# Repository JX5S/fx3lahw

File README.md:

# fx3lahw
Cypress FX3-based USB3 16ch 100Msps logic analyzer

Warning: current revision doesn't work

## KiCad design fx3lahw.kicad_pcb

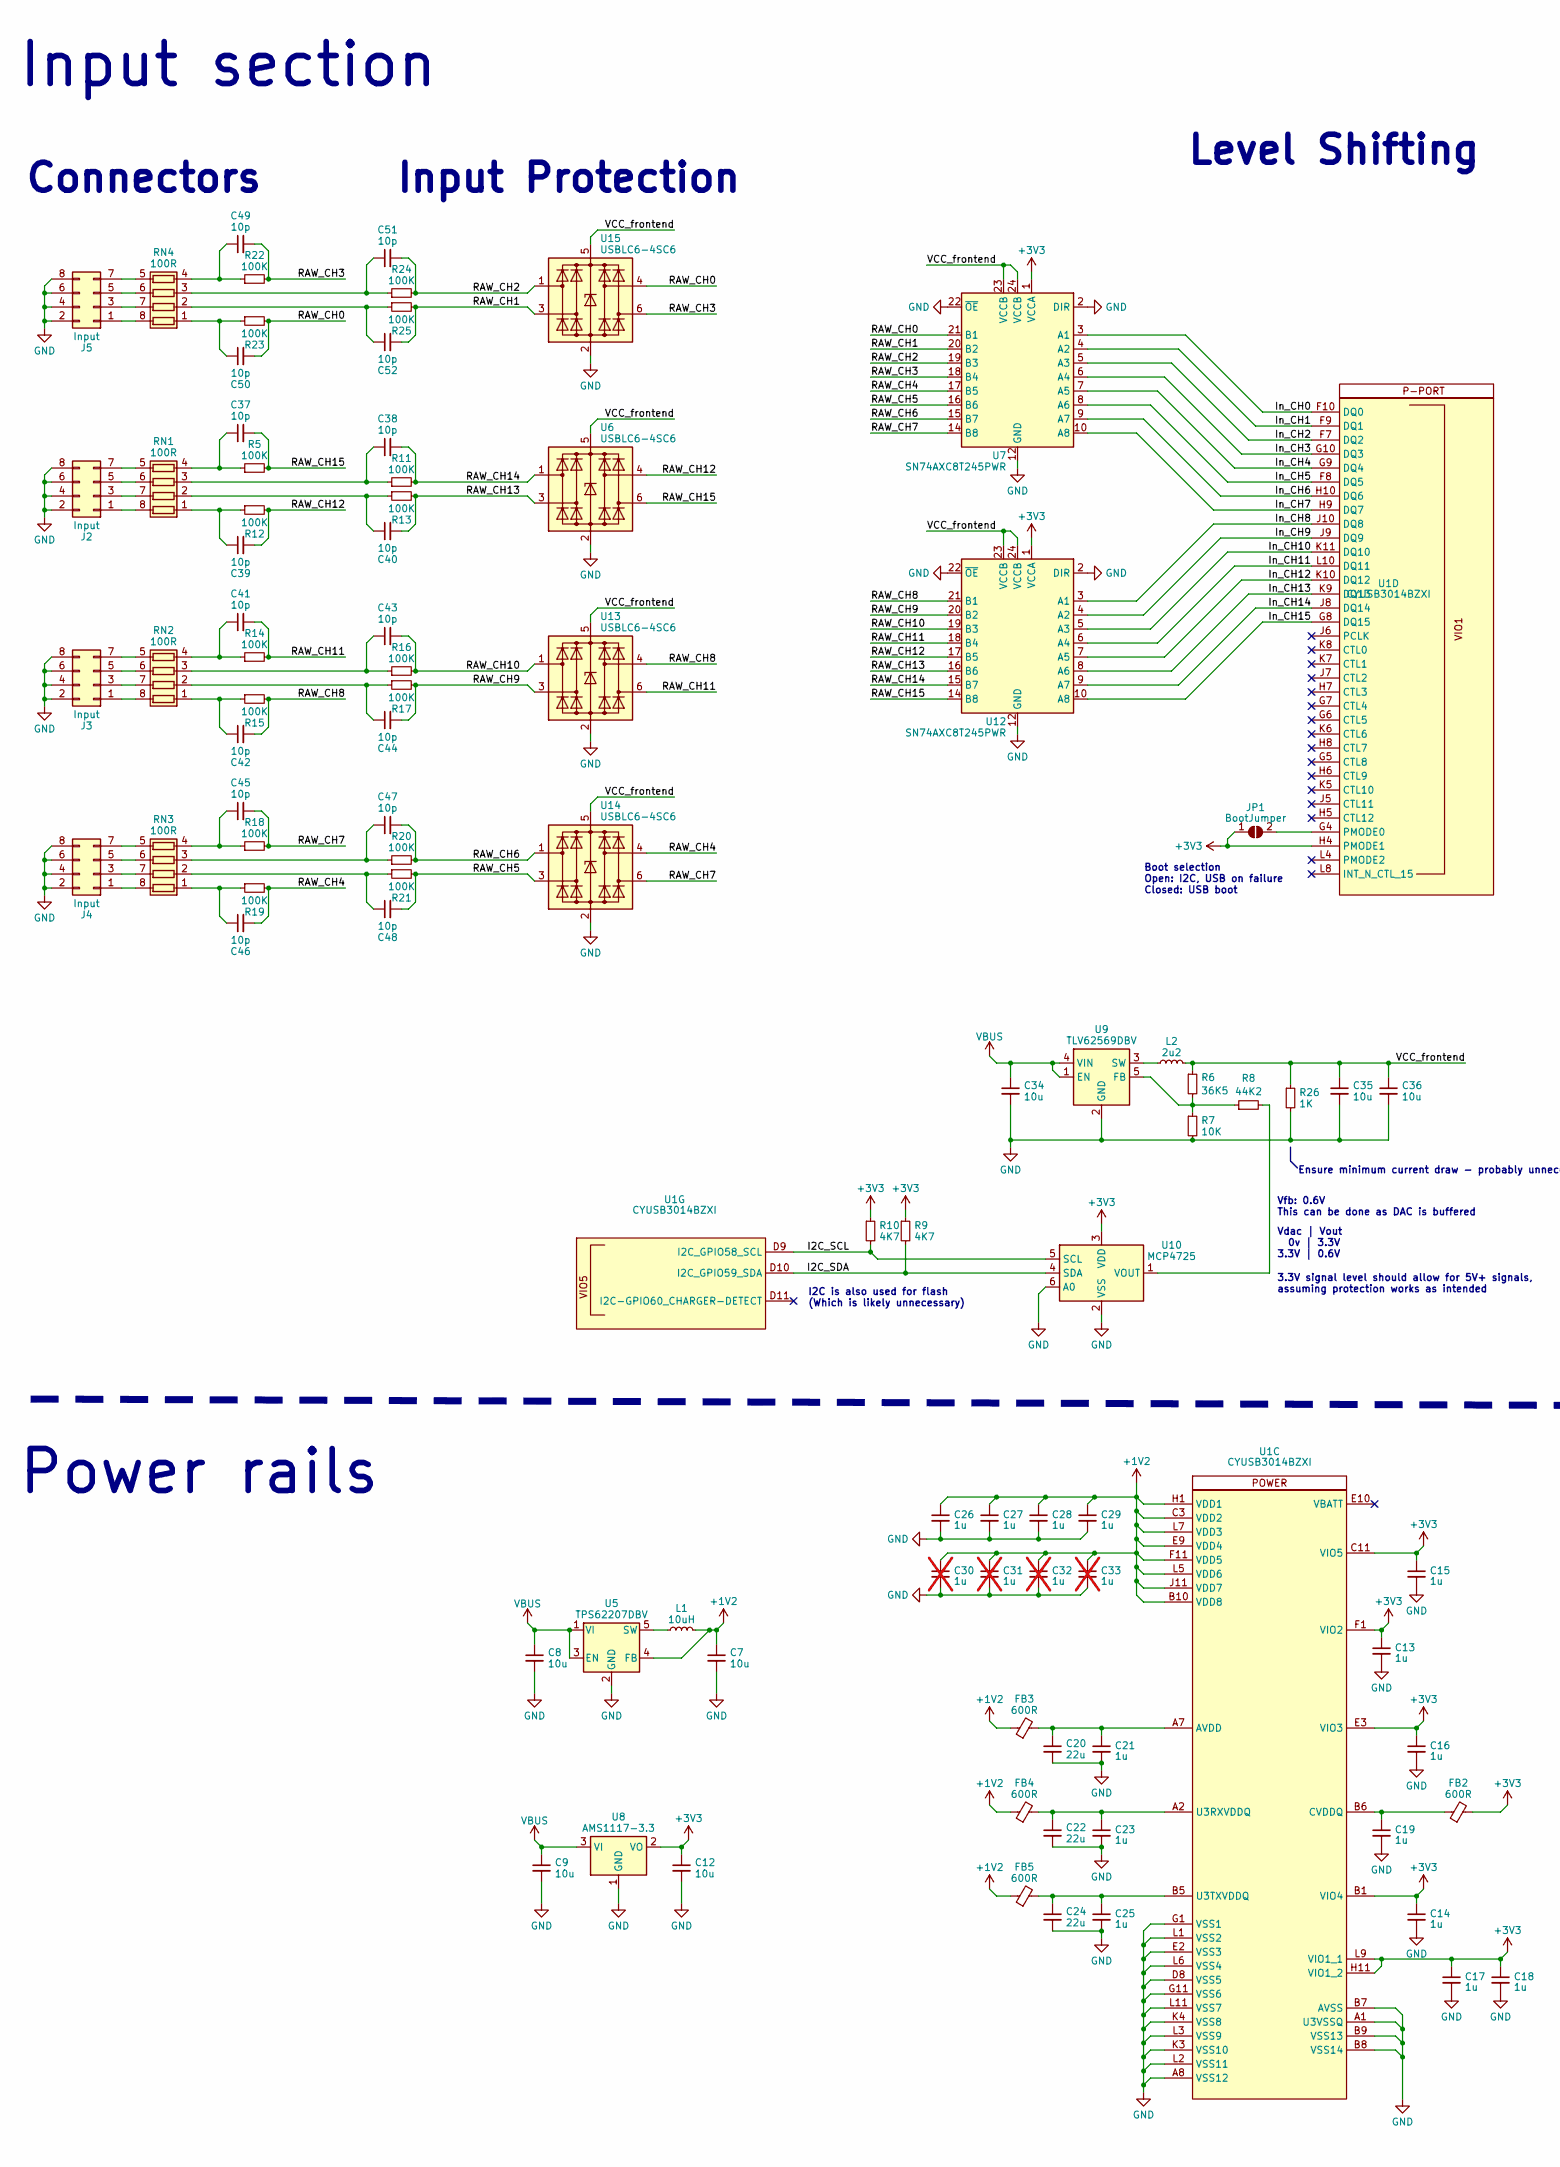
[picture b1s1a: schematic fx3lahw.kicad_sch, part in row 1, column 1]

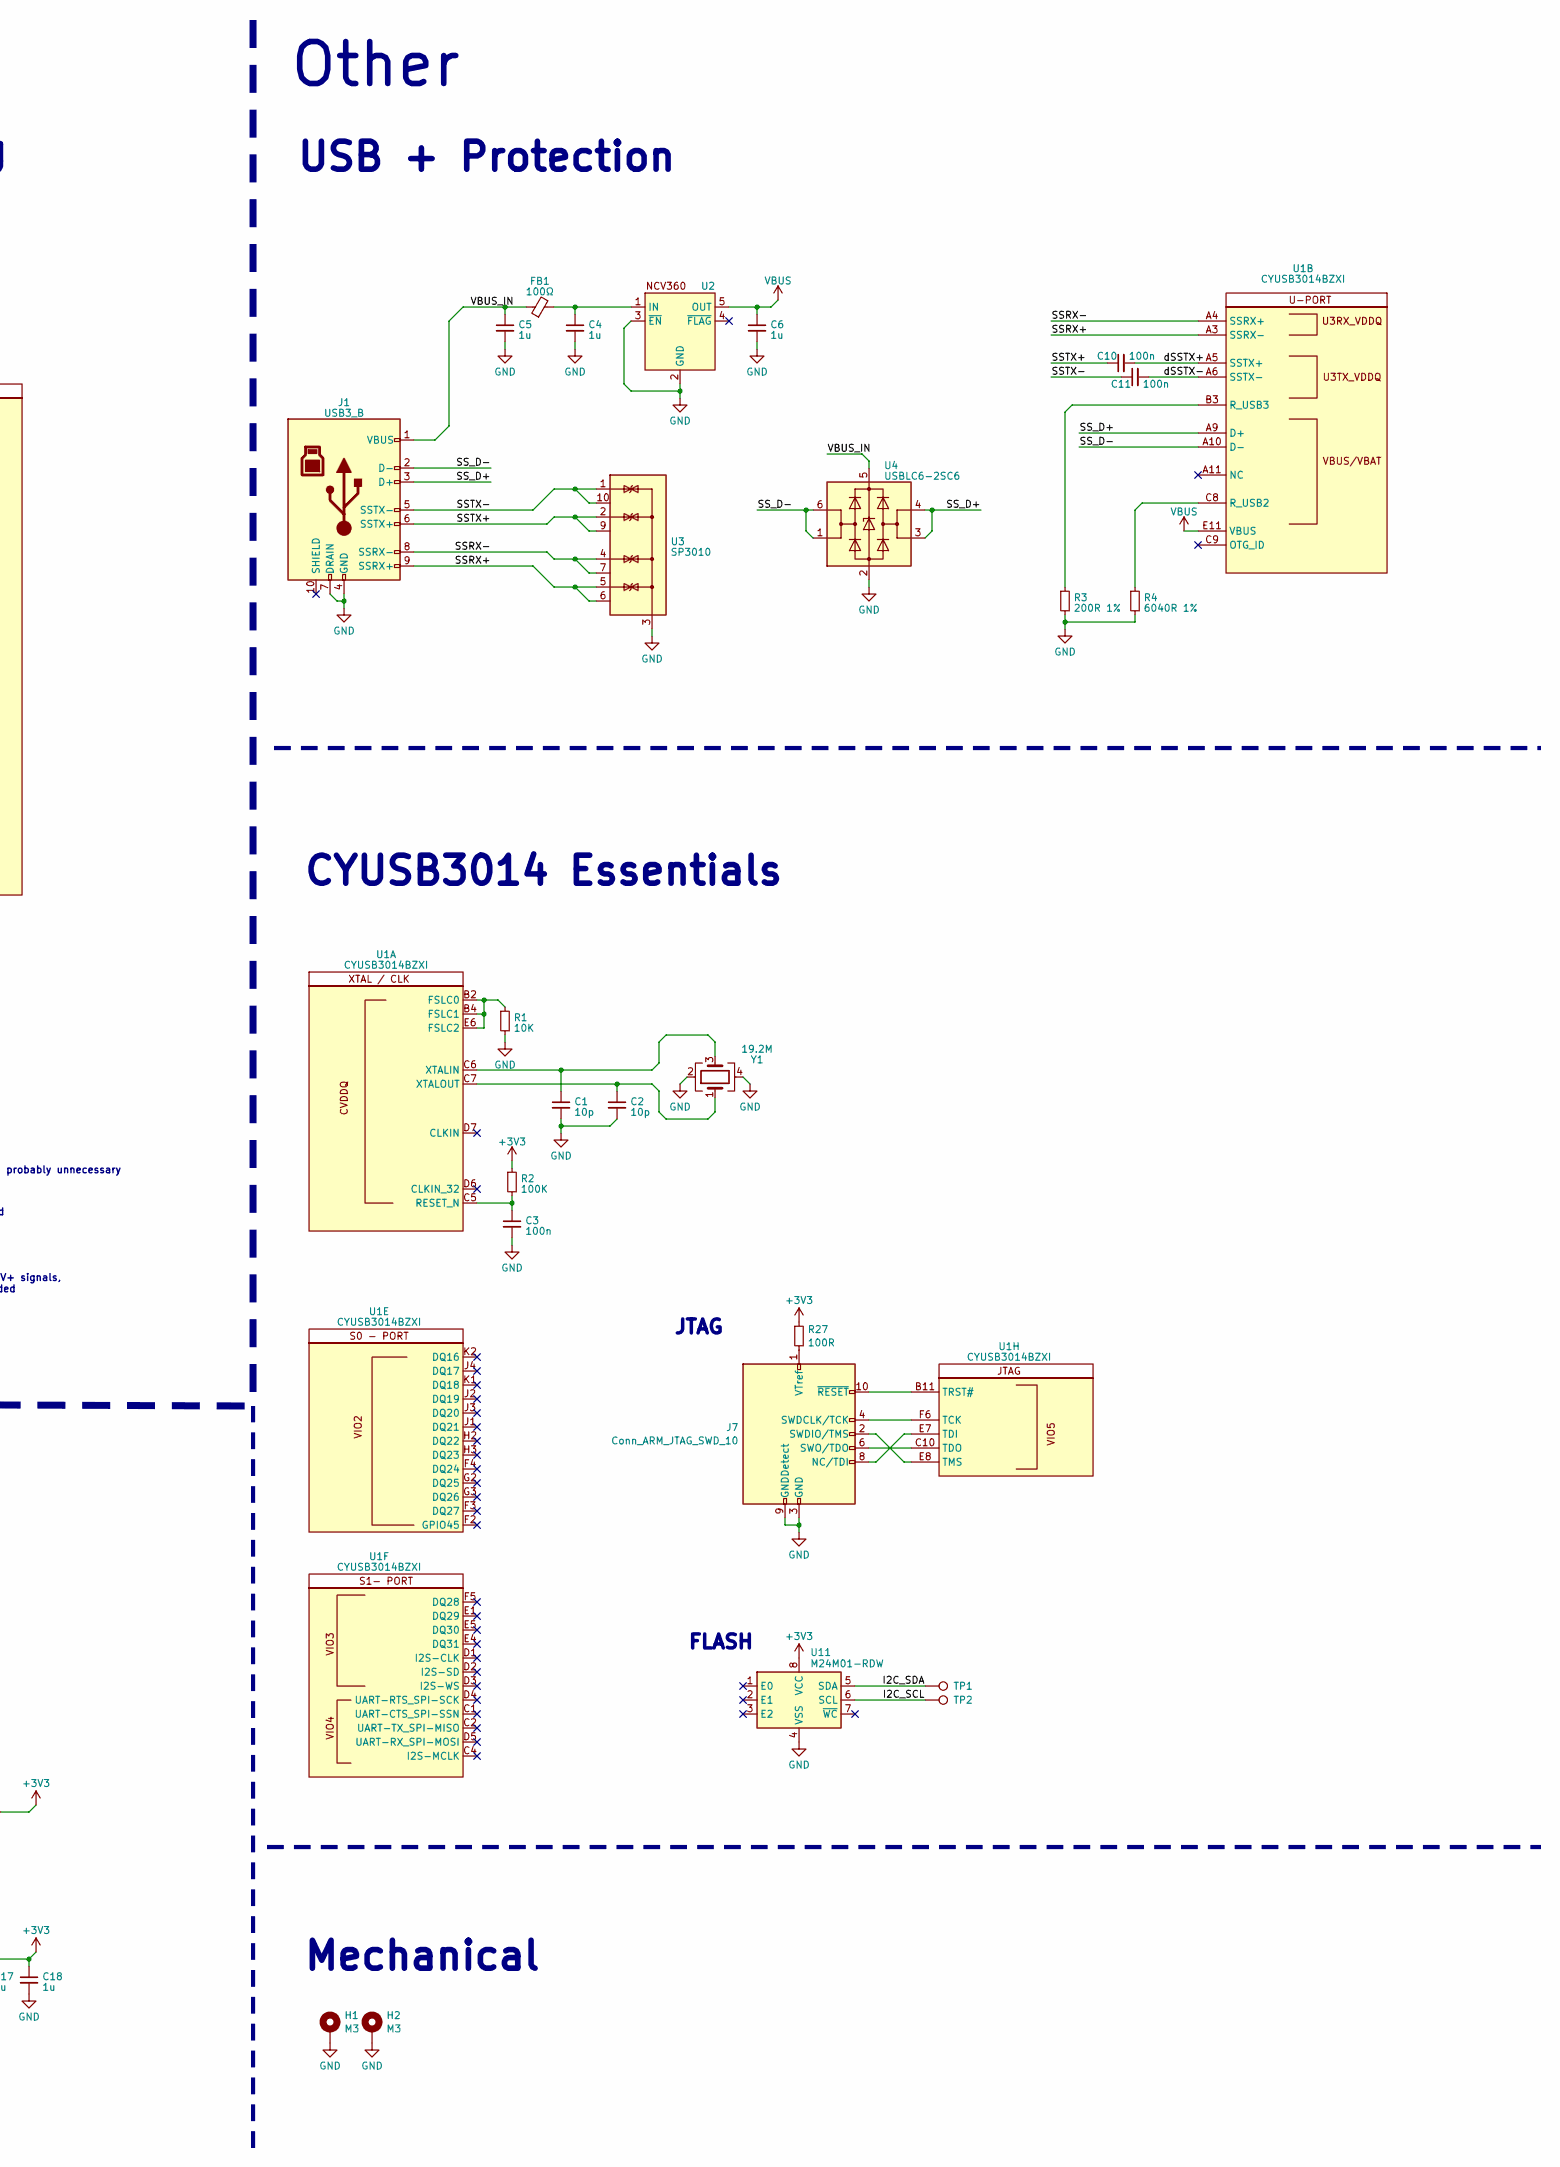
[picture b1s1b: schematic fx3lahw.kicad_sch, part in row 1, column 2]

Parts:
C1, C2, C37, C38, C39, C40, C41, C42, C43, C44, C45, C46, C47, C48, C49, C50, C51, C52: 10p; C_0402_1005Metric; LCSC C1576
C3, C10, C11: 100n; C_0402_1005Metric; LCSC C307331
C4, C5, C6: 1u; C_0603_1608Metric; LCSC C15849
C7, C8, C9, C12: 10u; C_0603_1608Metric; LCSC C19702
C13, C14, C15, C16, C17, C18, C19, C21, C23, C25, C26, C27, C28, C29: 1u; C_0402_1005Metric; LCSC C52923
C20, C22, C24: 22u; C_0603_1608Metric; LCSC C59461
C30, C31, C32, C33: 1u; C_0402_1005Metric; LCSC C52923; not fitted
C34, C35, C36: 10u; C_0603_1608Metric; LCSC C96446
FB1: 100Ω; R_0805_2012Metric; LCSC C1015
FB2, FB3, FB4, FB5: 600R; R_0603_1608Metric; LCSC C1002
H1, H2: M3; MountingHole_3.2mm_M3_Pad; LCSC .
J1: USB3_B; USB3_typeB; LCSC C105423
J2, J3, J4, J5: Input; PinHeader_2x04_P2.54mm_Horizontal; LCSC C492432
J7: Conn_ARM_JTAG_SWD_10; PinHeader_2x05_P1.27mm_Vertical_SMD; LCSC C2935458
JP1: BootJumper; SolderJumper-2_P1.3mm_Open_RoundedPad1.0x1.5mm
L1: 10uH; L_Sunlord_SWPA252012S; LCSC C88532
L2: 2u2; L_Sunlord_SWPA252012S; LCSC C88527
R1, R7: 10K; R_0402_1005Metric; LCSC C25744
R2, R5, R11, R12, R13, R14, R15, R16, R17, R18, R19, R20, R21, R22, R23, R24, R25: 100K; R_0402_1005Metric; LCSC C25741
R3: 200R 1%; R_0603_1608Metric; LCSC C8218
R4: 6040R 1%; R_0603_1608Metric; LCSC C2999565
R6: 36K5; R_0402_1005Metric; LCSC C15011
R8: 44K2; R_0402_1005Metric; LCSC C354260
R9, R10: 4K7; R_0603_1608Metric; LCSC C23162
R26: 1K; R_0603_1608Metric; LCSC C21190
R27: 100R; R_0402_1005Metric; LCSC C25076
RN1, RN2, RN3, RN4: 100R; R_Array_Convex_4x0603; LCSC C136838
TP1, TP2: TestPoint; TestPoint_Pad_D2.0mm
U1: CYUSB3014BZXI; XBGA-121_10x10mm_Layout11x11_P0.8mm; LCSC C462526
U2: SOT-23-5; LCSC C603912
U3: SP3010; USON-10_2.5x1.0mm_P0.5mm; LCSC C126837
U4: USBLC6-2SC6; SOT-23-6; LCSC C2827654
U5: TPS62207DBV; SOT-23-5; LCSC C398350
U6, U13, U14, U15: USBLC6-4SC6; SOT-23-6; LCSC C5180279
U7, U12: SN74AXC8T245PWR; TSSOP-24_4.4x7.8mm_P0.65mm; LCSC C882718
U8: AMS1117-3.3; SOT-223-3_TabPin2; LCSC C6186
U9: TLV62569DBV; SOT-23-5; LCSC C141836
U10: MCP4725; SOT-23-6; LCSC C144198
U11: M24M01-RDW; TSSOP-8_4.4x3mm_P0.65mm; LCSC C283500
Y1: 19.2M; Crystal_SMD_3225-4Pin_3.2x2.5mm; LCSC C426975

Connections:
+1V2: C7.1, C26.1, C27.1, C28.1, C29.1, C30.1, C31.1, C32.1, C33.1, FB3.1, FB4.1, FB5.1, L1.2, U1.B10 (VDD8), U1.C3 (VDD2), U1.E9 (VDD4), U1.F11 (VDD5), U1.H1 (VDD1), U1.J11 (VDD7), U1.L5 (VDD6), U1.L7 (VDD3), U5.4 (FB)
+3V3: C12.1, C13.1, C14.1, C15.1, C16.1, C17.1, C18.1, FB2.2, JP1.1 (A), R2.1, R9.1, R10.1, R27.1, U1.B1 (VIO4), U1.C11 (VIO5), U1.E3 (VIO3), U1.F1 (VIO2), U1.H4 (PMODE1), U1.H11 (VIO1_2), U1.L9 (VIO1_1), U7.1 (VCCA), U8.2 (VO), U10.3 (VDD), U11.8 (VCC), U12.1 (VCCA)
/I2C_SCL: R10.2, TP2.1, U1.D9 (I2C_GPIO58_SCL), U10.5 (SCL), U11.6 (SCL)
/I2C_SDA: R9.2, TP1.1, U1.D10 (I2C_GPIO59_SDA), U10.4 (SDA), U11.5 (SDA)
/In_CH0: U1.F10 (DQ0), U7.3 (A1)
/In_CH1: U1.F9 (DQ1), U7.4 (A2)
/In_CH2: U1.F7 (DQ2), U7.5 (A3)
/In_CH3: U1.G10 (DQ3), U7.6 (A4)
/In_CH4: U1.G9 (DQ4), U7.7 (A5)
/In_CH5: U1.F8 (DQ5), U7.8 (A6)
/In_CH6: U1.H10 (DQ6), U7.9 (A7)
/In_CH7: U1.H9 (DQ7), U7.10 (A8)
/In_CH8: U1.J10 (DQ8), U12.3 (A1)
/In_CH9: U1.J9 (DQ9), U12.4 (A2)
/In_CH10: U1.K11 (DQ10), U12.5 (A3)
/In_CH11: U1.L10 (DQ11), U12.6 (A4)
/In_CH12: U1.K10 (DQ12), U12.7 (A5)
/In_CH13: U1.K9 (DQ13), U12.8 (A6)
/In_CH14: U1.J8 (DQ14), U12.9 (A7)
/In_CH15: U1.G8 (DQ15), U12.10 (A8)
/RAW_CH0: C50.2, R23.2, U7.21 (B1), U15.4 (I/O3)
/RAW_CH1: C52.2, R25.2, U7.20 (B2), U15.3 (I/O2)
/RAW_CH2: C51.2, R24.2, U7.19 (B3), U15.1 (I/O1)
/RAW_CH3: C49.2, R22.2, U7.18 (B4), U15.6 (I/O4)
/RAW_CH4: C46.2, R19.2, U7.17 (B5), U14.4 (I/O3)
/RAW_CH5: C48.2, R21.2, U7.16 (B6), U14.3 (I/O2)
/RAW_CH6: C47.2, R20.2, U7.15 (B7), U14.1 (I/O1)
/RAW_CH7: C45.2, R18.2, U7.14 (B8), U14.6 (I/O4)
/RAW_CH8: C42.2, R15.2, U12.21 (B1), U13.4 (I/O3)
/RAW_CH9: C44.2, R17.2, U12.20 (B2), U13.3 (I/O2)
/RAW_CH10: C43.2, R16.2, U12.19 (B3), U13.1 (I/O1)
/RAW_CH11: C41.2, R14.2, U12.18 (B4), U13.6 (I/O4)
/RAW_CH12: C39.2, R12.2, U6.4 (I/O3), U12.17 (B5)
/RAW_CH13: C40.2, R13.2, U6.3 (I/O2), U12.16 (B6)
/RAW_CH14: C38.2, R11.2, U6.1 (I/O1), U12.15 (B7)
/RAW_CH15: C37.2, R5.2, U6.6 (I/O4), U12.14 (B8)
/SSRX+: J1.9 (SSRX+), U1.A3 (SSRX-), U3.5 (IO4), U3.6 (NC)
/SSRX-: J1.8 (SSRX-), U1.A4 (SSRX+), U3.4 (IO3), U3.7 (NC)
/SSTX+: C10.1, J1.6 (SSTX+), U3.2 (IO2), U3.9 (NC)
/SSTX-: C11.1, J1.5 (SSTX-), U3.1 (IO1), U3.10 (NC)
/SS_D+: J1.3 (D+), U1.A9 (D+), U4.3 (I/O2), U4.4 (I/O2)
/SS_D-: J1.2 (D-), U1.A10 (D-), U4.1 (I/O1), U4.6 (I/O1)
/VBUS_IN: C5.1, FB1.1, J1.1 (VBUS), U4.5 (VBUS)
/VCC_frontend: C35.1, C36.1, L2.2, R6.1, R26.1, U6.5 (VBUS), U7.23 (VCCB), U7.24 (VCCB), U12.23 (VCCB), U12.24 (VCCB), U13.5 (VBUS), U14.5 (VBUS), U15.5 (VBUS)
/dSSTX+: C10.2, U1.A5 (SSTX+)
/dSSTX-: C11.2, U1.A6 (SSTX-)
GND: C1.2, C2.2, C3.2, C4.2, C5.2, C6.2, C7.2, C8.2, C9.2, C12.2, C13.2, C14.2, C15.2, C16.2, C17.2, C18.2, C19.2, C20.2, C21.2, C22.2, C23.2, C24.2, C25.2, C26.2, C27.2, C28.2, C29.2, C30.2, C31.2, C32.2, C33.2, C34.2, C35.2, C36.2, H1.1, H2.1, J1.4 (GND), J1.7 (DRAIN), J2.2, J2.4, J2.6, J2.8, J3.2, J3.4, J3.6, J3.8, J4.2, J4.4, J4.6, J4.8, J5.2, J5.4, J5.6, J5.8, J7.3 (GND), J7.5 (GND), J7.9 (GNDDetect), R1.2, R3.2, R4.2, R7.2, R26.2, U1.A1 (U3VSSQ), U1.A8 (VSS12), U1.B7 (AVSS), U1.B8 (VSS14), U1.B9 (VSS13), U1.D8 (VSS5), U1.E2 (VSS3), U1.G1 (VSS1), U1.G11 (VSS6), U1.K3 (VSS10), U1.K4 (VSS8), U1.L1 (VSS2), U1.L2 (VSS11), U1.L3 (VSS9), U1.L6 (VSS4), U1.L11 (VSS7), U2.2 (GND), U2.3 (~EN), U3.3 (G), U3.8 (G), U4.2 (GND), U5.2 (GND), U6.2 (GND), U7.2 (DIR), U7.11 (DIR2), U7.12 (GND), U7.13 (GND), U7.22 (~OE), U8.1 (GND), U9.2 (GND), U10.2 (VSS), U10.6 (A0), U11.4 (VSS), U12.2 (DIR), U12.11 (DIR2), U12.12 (GND), U12.13 (GND), U12.22 (~OE), U13.2 (GND), U14.2 (GND), U15.2 (GND), Y1.2, Y1.4
unnamed: J2.1, RN1.8 (R1.2)
unnamed: J2.3, RN1.7 (R2.2)
unnamed: J2.5, RN1.6 (R3.2)
unnamed: J2.7, RN1.5 (R4.2)
unnamed: J3.1, RN2.8 (R1.2)
unnamed: J3.3, RN2.7 (R2.2)
unnamed: J3.5, RN2.6 (R3.2)
unnamed: J3.7, RN2.5 (R4.2)
unnamed: J4.1, RN3.8 (R1.2)
unnamed: J4.3, RN3.7 (R2.2)
unnamed: J4.5, RN3.6 (R3.2)
unnamed: J4.7, RN3.5 (R4.2)
unnamed: J5.1, RN4.8 (R1.2)
unnamed: J5.3, RN4.7 (R2.2)
unnamed: J5.5, RN4.6 (R3.2)
unnamed: J5.7, RN4.5 (R4.2)
unnamed: J7.8 (NC/TDI), U1.E7 (TDI)
unnamed: J7.4 (SWDCLK/TCK), U1.F6 (TCK)
unnamed: J7.2 (SWDIO/TMS), U1.E8 (TMS)
unnamed: J7.6 (SWO/TDO), U1.C10 (TDO)
unnamed: J7.1 (VTref), R27.2
unnamed: J7.10 (~RESET), U1.B11 (TRST#)
unnamed: JP1.2 (B), U1.G4 (PMODE0)
unnamed: C39.1, R12.1, RN1.1 (R1.1)
unnamed: C40.1, R13.1, RN1.2 (R2.1)
unnamed: C38.1, R11.1, RN1.3 (R3.1)
unnamed: C37.1, R5.1, RN1.4 (R4.1)
unnamed: C42.1, R15.1, RN2.1 (R1.1)
unnamed: C44.1, R17.1, RN2.2 (R2.1)
unnamed: C43.1, R16.1, RN2.3 (R3.1)
unnamed: C41.1, R14.1, RN2.4 (R4.1)
unnamed: C46.1, R19.1, RN3.1 (R1.1)
unnamed: C48.1, R21.1, RN3.2 (R2.1)
unnamed: C47.1, R20.1, RN3.3 (R3.1)
unnamed: C45.1, R18.1, RN3.4 (R4.1)
unnamed: C50.1, R23.1, RN4.1 (R1.1)
unnamed: C52.1, R25.1, RN4.2 (R2.1)
unnamed: C51.1, R24.1, RN4.3 (R3.1)
unnamed: C49.1, R22.1, RN4.4 (R4.1)
unnamed: R1.1, U1.B2 (FSLC0), U1.B4 (FSLC1), U1.E6 (FSLC2)
unnamed: C3.1, R2.2, U1.C5 (RESET_N)
unnamed: C1.1, U1.C6 (XTALIN), Y1.3
unnamed: C2.1, U1.C7 (XTALOUT), Y1.1
unnamed: R4.1, U1.C8 (R_USB2)
unnamed: R3.1, U1.B3 (R_USB3)
unnamed: C20.1, C21.1, FB3.2, U1.A7 (AVDD)
unnamed: C19.1, FB2.1, U1.B6 (CVDDQ)
unnamed: C22.1, C23.1, FB4.2, U1.A2 (U3RXVDDQ)
unnamed: C24.1, C25.1, FB5.2, U1.B5 (U3TXVDDQ)
unnamed: C4.1, FB1.2, U2.1 (IN)
unnamed: L1.1, U5.5 (SW)
unnamed: R6.2, R7.1, R8.1, U9.5 (FB)
unnamed: L2.1, U9.3 (SW)
unnamed: R8.2, U10.1 (VOUT)
VBUS: C6.1, C8.1, C9.1, C34.1, U1.E11 (VBUS), U2.5 (OUT), U5.1 (VI), U5.3 (EN), U8.3 (VI), U9.1 (EN), U9.4 (VIN)

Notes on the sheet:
Vfb: 0.6V This can be done as DAC is buffered
Power rails
Vdac | Vout 0v | 3.3V 3.3V | 0.6V
Other
USB + Protection
Level Shifting
CYUSB3014 Essentials
Mechanical
FLASH
Connectors
3.3V signal level should allow for 5V+ signals, assuming protection works as intended
JTAG
Ensure minimum current draw - probably unnecessary
Input Protection
Input section
I2C is also used for flash (Which is likely unnecessary)
Boot selection Open: I2C, USB on failure Closed: USB boot

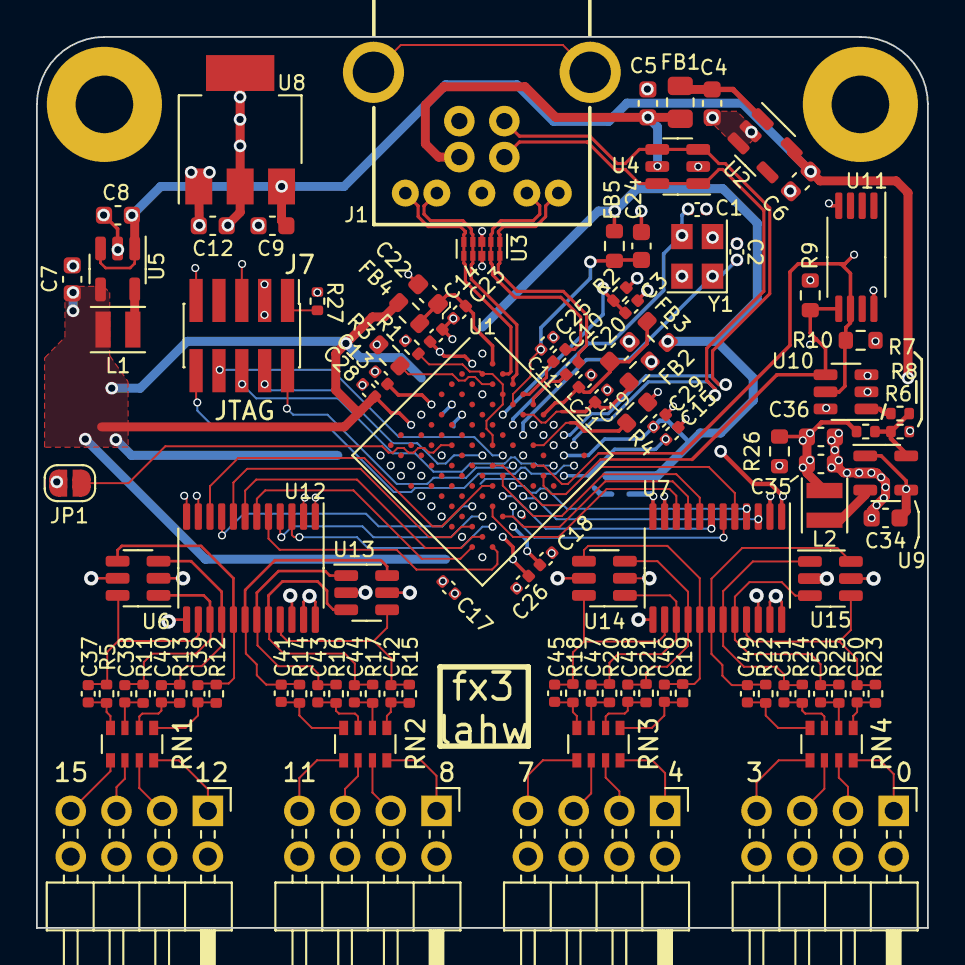
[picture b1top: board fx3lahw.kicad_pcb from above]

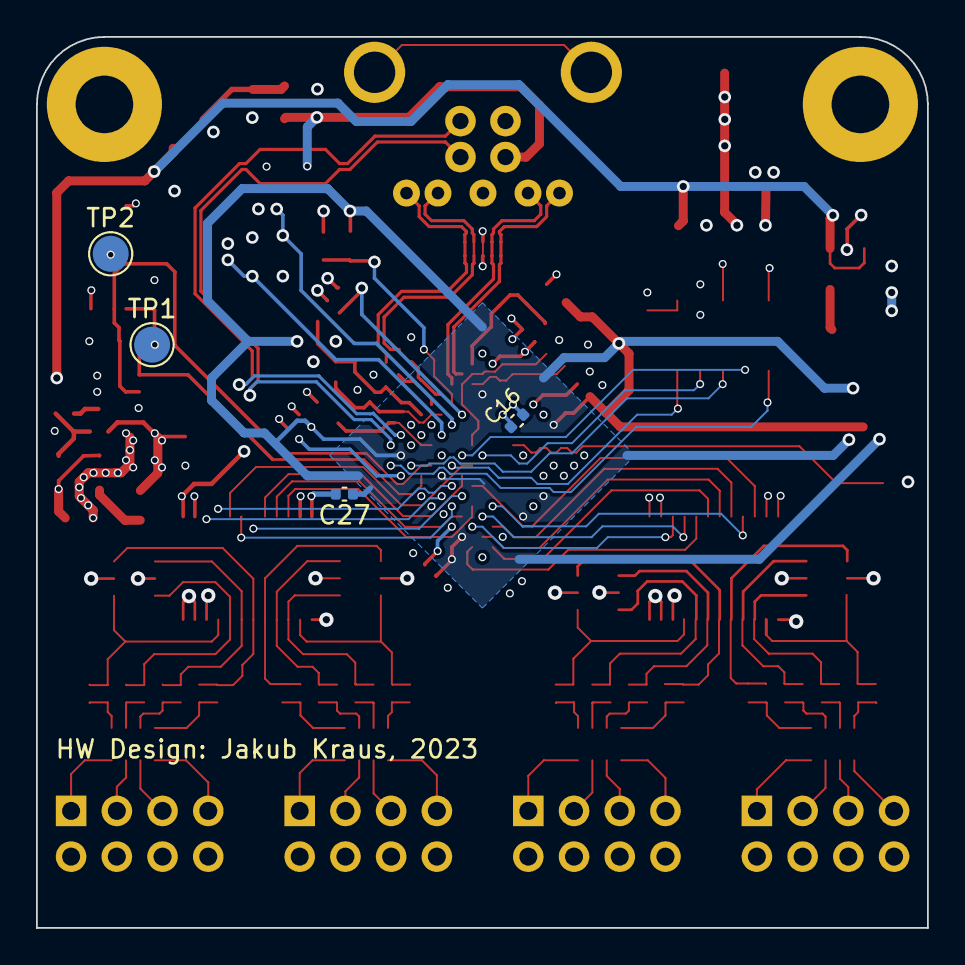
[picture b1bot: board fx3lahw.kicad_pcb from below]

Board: 6 copper layers, 49.5 x 49.5 mm, 113 parts (4 on the bottom side), 102 nets.

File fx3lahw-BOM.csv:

"Source:","C:\dev\KiCad\fx3lahw\fx3lahw.kicad_sch"
"Date:","10/15/2023 1:48:04 PM"
"Tool:","Eeschema 7.0.6"
"Generator:","C:\Program Files\KiCad\7.0\bin\scripting\plugins/bom_csv_grouped_by_value.py"
"Component Count:","117"

"Collated Components:"

"Item","Qty","Reference(s)","Value","LibPart","Footprint","Datasheet","DNP","LCSC"
"1","18","C1, C2, C37, C38, C39, C40, C41, C42, C43, C44, C45, C46, C47, C48, C49, C50, C51, C52","10p","Device:C_Small","Capacitor_SMD:C_0402_1005Metric","~","","C1576"
"2","3","C3, C10, C11","100n","Device:C_Small","Capacitor_SMD:C_0402_1005Metric","~","","C307331"
"3","3","C4, C5, C6","1u","Device:C_Small","Capacitor_SMD:C_0603_1608Metric","~","","C15849"
"4","7","C7, C8, C9, C12, C34, C35, C36","10u","Device:C_Small","Capacitor_SMD:C_0603_1608Metric","~","","C19702"
"5","14","C13, C14, C15, C16, C17, C18, C19, C21, C23, C25, C26, C27, C28, C29","1u","Device:C_Small","Capacitor_SMD:C_0402_1005Metric","~","","C52923"
"6","3","C20, C22, C24","22u","Device:C_Small","Capacitor_SMD:C_0603_1608Metric","~","","C59461"
"7","4","C30, C31, C32, C33","1u","Device:C_Small","Capacitor_SMD:C_0402_1005Metric","~","DNP","C52923"
"8","1","FB1","100Ω","Device:FerriteBead_Small","Resistor_SMD:R_0805_2012Metric","~","","C1015"
"9","4","FB2, FB3, FB4, FB5","600R","Device:FerriteBead_Small","Resistor_SMD:R_0603_1608Metric","~","","C1002"
"10","2","H1, H2","M3","Mechanical:MountingHole_Pad","MountingHole:MountingHole_3.2mm_M3_Pad","~","","."
"11","1","J1","USB3_B","Connector:USB3_B","libraries:USB3_typeB","~",""," C105423"
"12","4","J2, J3, J4, J5","Input","Connector_Generic:Conn_02x04_Odd_Even","Connector_PinHeader_2.54mm:PinHeader_2x04_P2.54mm_Horizontal","~","","C492432"
"13","1","J7","Conn_ARM_JTAG_SWD_10","Connector:Conn_ARM_JTAG_SWD_10","Connector_PinHeader_1.27mm:PinHeader_2x05_P1.27mm_Vertical_SMD","http://infocenter.arm.com/help/topic/com.arm.doc.ddi0314h/DD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","","C2935458"
"14","1","JP1","SolderJumper_2_Open","Jumper:SolderJumper_2_Open","Jumper:SolderJumper-2_P1.3mm_Open_RoundedPad1.0x1.5mm","~","","-"
"15","1","L1","10uH","Device:L_Small","Inductor_SMD:L_Sunlord_SWPA252012S","~","","C88532"
"16","1","L2","2u2","Device:L_Small","Inductor_SMD:L_Sunlord_SWPA252012S","~","","C88527"
"17","2","R1, R7","10K","Device:R_Small","Resistor_SMD:R_0402_1005Metric","~","","C25744"
"18","17","R2, R5, R11, R12, R13, R14, R15, R16, R17, R18, R19, R20, R21, R22, R23, R24, R25","100K","Device:R_Small","Resistor_SMD:R_0402_1005Metric","~","","C25741"
"19","1","R3","200R 1%","Device:R_Small","Resistor_SMD:R_0603_1608Metric","~","","C8218"
"20","1","R4","6040R 1%","Device:R_Small","Resistor_SMD:R_0603_1608Metric","~","","C2999565"
"21","1","R6","36K5","Device:R_Small","Resistor_SMD:R_0402_1005Metric","~","","C15011"
"22","1","R8","44K2","Device:R_Small","Resistor_SMD:R_0402_1005Metric","~","","C354260"
"23","2","R9, R10","4K7","Device:R_Small","Resistor_SMD:R_0603_1608Metric","~","","C23162"
"24","1","R26","1K","Device:R_Small","Resistor_SMD:R_0603_1608Metric","~","","C21190"
"25","1","R27","100R","Device:R_Small","Resistor_SMD:R_0402_1005Metric","~","","C25076"
"26","4","RN1, RN2, RN3, RN4","100R","Device:R_Pack04","Resistor_SMD:R_Array_Convex_4x0603","~","","C136838"
"27","2","TP1, TP2","TestPoint","Connector:TestPoint","TestPoint:TestPoint_Pad_D2.0mm","~","",""
"28","1","U1","CYUSB3014BZXI",":CYUSB3014BZXI_1","Package_BGA:XBGA-121_10x10mm_Layout11x11_P0.8mm","","","C462526"
"29","1","U2","~","fx3lahw_symbols:NCV360SN","Package_TO_SOT_SMD:SOT-23-5","https://datasheet.lcsc.com/lcsc/2108140130_onsemi-NCV360SNT1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","","C603912"
"30","1","U3","SP3010","Power_Protection:TPD4E02B04DQA","Package_SON:USON-10_2.5x1.0mm_P0.5mm","https://datasheet.lcsc.com/lcsc/1809191831_Littelfuse-SP3010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","","C126837"
"31","1","U4","USBLC6-2SC6","Power_Protection:USBLC6-2SC6","Package_TO_SOT_SMD:SOT-23-6","https://www.st.com/resource/en/datasheet/usblc6-2.pdf","","C2827654"
"32","1","U5","TPS62207DBV","Regulator_Switching:TPS62207DBV","Package_TO_SOT_SMD:SOT-23-5","http://www.ti.com/lit/ds/symlink/tps62201.pdf","","C398350"
"33","4","U6, U13, U14, U15","USBLC6-4SC6","Power_Protection:USBLC6-4SC6","Package_TO_SOT_SMD:SOT-23-6","https://www.st.com/resource/en/datasheet/usblc6-4.pdf","","C5180279"
"34","2","U7, U12","SN74AXC8T245PWR","Library:SN74AVC8T245PW","Package_SO:TSSOP-24_4.4x7.8mm_P0.65mm","https://www.ti.com/lit/ds/symlink/sn74avc8t245.pdf","","C882718"
"35","1","U8","AMS1117-3.3","Regulator_Linear:AMS1117-3.3","Package_TO_SOT_SMD:SOT-223-3_TabPin2","http://www.advanced-monolithic.com/pdf/ds1117.pdf","","C6186"
"36","1","U9","TLV62569DBV","Regulator_Switching:TLV62569DBV","Package_TO_SOT_SMD:SOT-23-5","http://www.ti.com/lit/ds/symlink/tlv62569.pdf","","C141836"
"37","1","U10","MCP4725","Analog_DAC:MCP4725xxx-xCH","Package_TO_SOT_SMD:SOT-23-6","http://ww1.microchip.com/downloads/en/DeviceDoc/22039d.pdf","","C144198"
"38","1","U11","M24M01-RDW","Memory_EEPROM:M24C02-RDW","Package_SO:TSSOP-8_4.4x3mm_P0.65mm","http://www.st.com/content/ccc/resource/technical/document/da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","","C283500"
"39","1","Y1","19.2M","Device:Crystal_GND24","Crystal:Crystal_SMD_3225-4Pin_3.2x2.5mm","~","","C426975"

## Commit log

2023-10-20 Update LICENSE
    Change license to CC-BY-SA
2023-10-20 Initial commit
    Initial commit
2023-10-21 Added picture of 3D view
2023-10-21 Update README.md
    Added picture to readme
2023-12-04 Add warning
